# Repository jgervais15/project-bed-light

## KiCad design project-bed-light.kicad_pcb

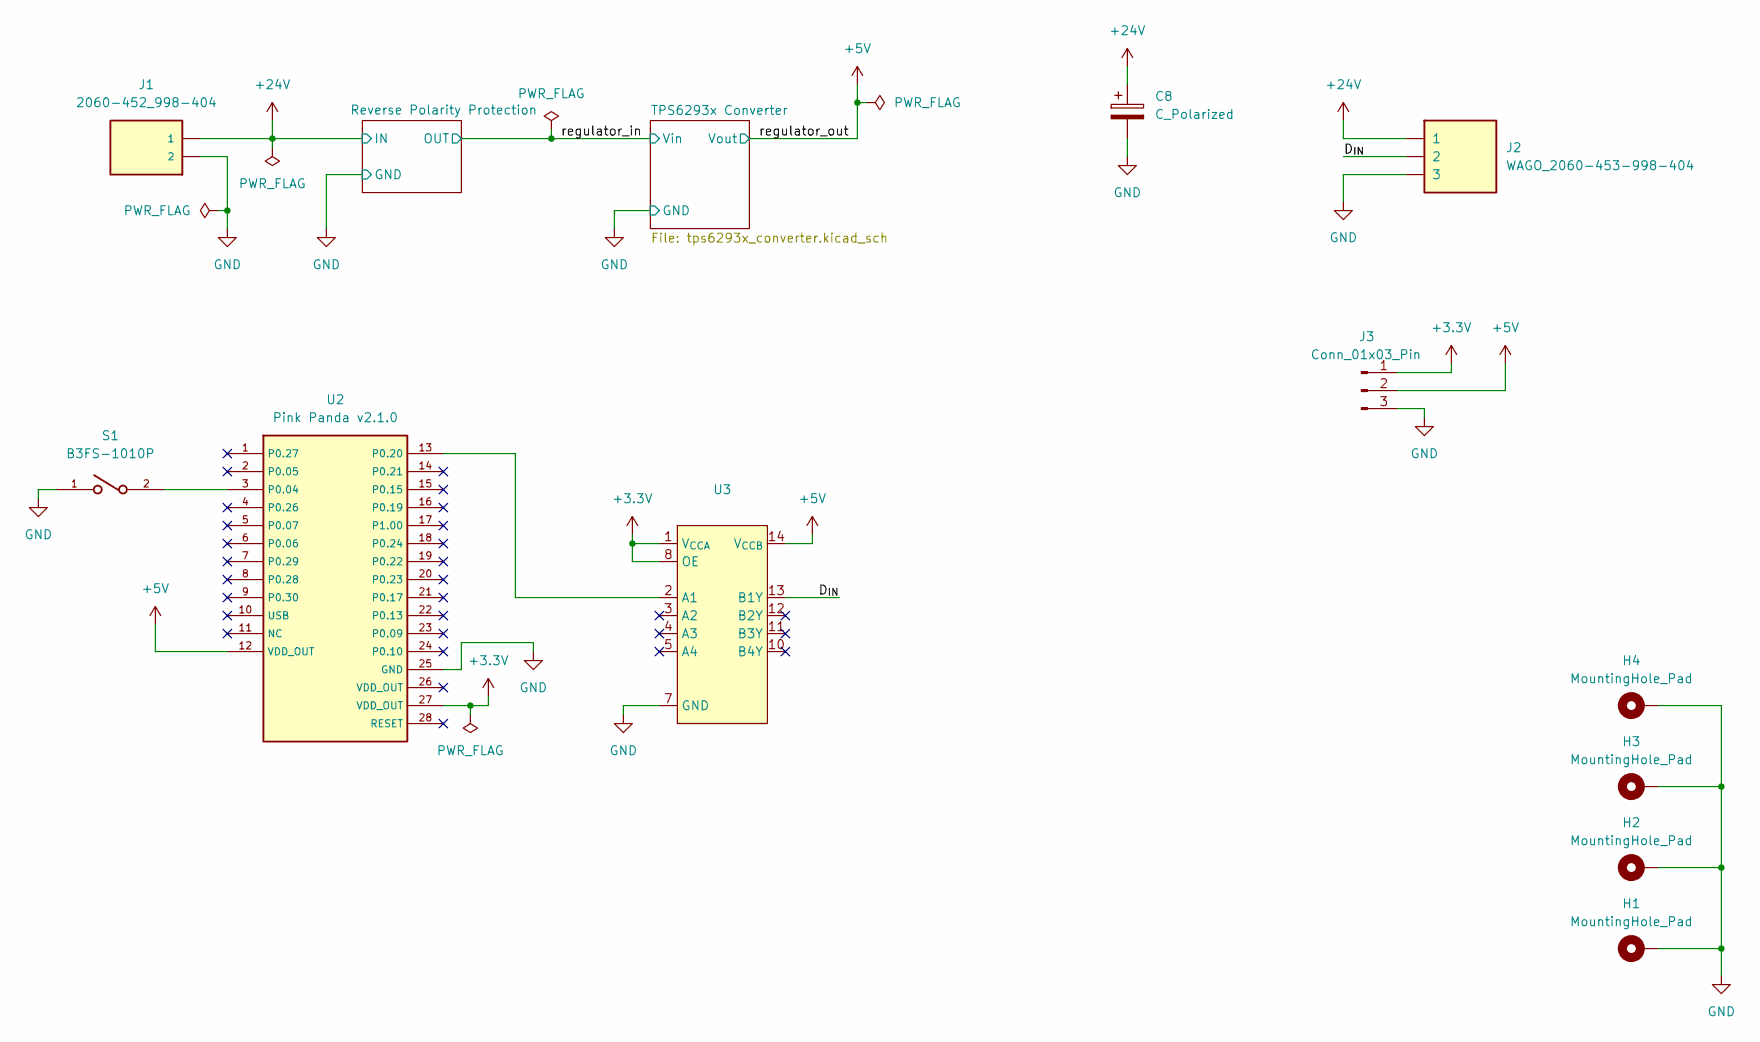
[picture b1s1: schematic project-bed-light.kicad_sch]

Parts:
C8: C_Polarized; CP_Elec_10x10
H1, H2, H3, H4: MountingHole_Pad; MountingHole_2.7mm_M2.5_ISO7380_Pad
J1: 2060-452_998-404; WAGO_2060-452_998-404; PARTREV N/A
J2: WAGO_2060-453-998-404
J3: Conn_01x03_Pin; PinHeader_1x03_P2.54mm_Vertical
S1: B3FS-1010P; SW_B3FS-1010P
U2: Pink Panda v2.1.0; pink_panda_SMD
U3: TSSOP-14_4.4x5mm_P0.65mm

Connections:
+3.3V: J3.1, U2.27 (VDD_OUT), U3.1 (V_{CCA}), U3.8 (OE)
+5V: J3.2, U2.12 (VDD_OUT), U3.14 (V_{CCB}); also elsewhere on the board
+24V: C8.1, J1.1_1 (1), J1.1_2 (1), J2.1_1 (1), J2.1_2 (1); also elsewhere on the board
/D_{IN}: J2.2_1 (2), J2.2_2 (2), U3.13 (B1Y)
GND: C8.2, H1.1, H2.1, H3.1, H4.1, J1.2_1 (2), J1.2_2 (2), J2.3_1 (3), J2.3_2 (3), J3.3, S1.1, U2.25 (GND), U3.7 (GND); also elsewhere on the board
unnamed: S1.2, U2.3 (P0.04)
unnamed: U2.13 (P0.20), U3.2 (A1)

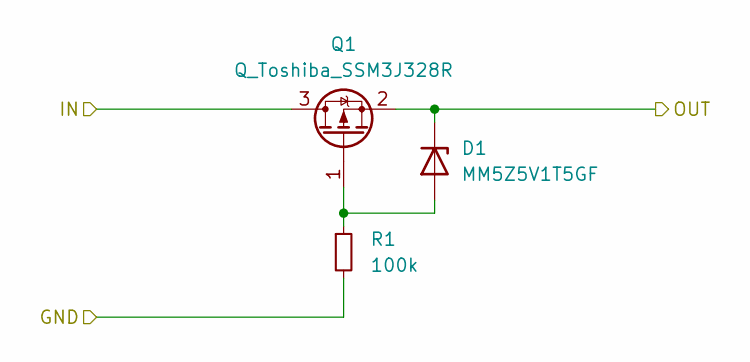
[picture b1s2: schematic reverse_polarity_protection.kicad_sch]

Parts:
D1: MM5Z5V1T5GF; D_SOD-523
Q1: Q_Toshiba_SSM3J328R; SOT-23F
R1: 100k; R_0603_1608Metric

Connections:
+24V: Q1.3 (D); also elsewhere on the board
/regulator_in: D1.1 (K), Q1.2 (S); also elsewhere on the board
GND: R1.2; also elsewhere on the board
unnamed: D1.2 (A), Q1.1 (G), R1.1

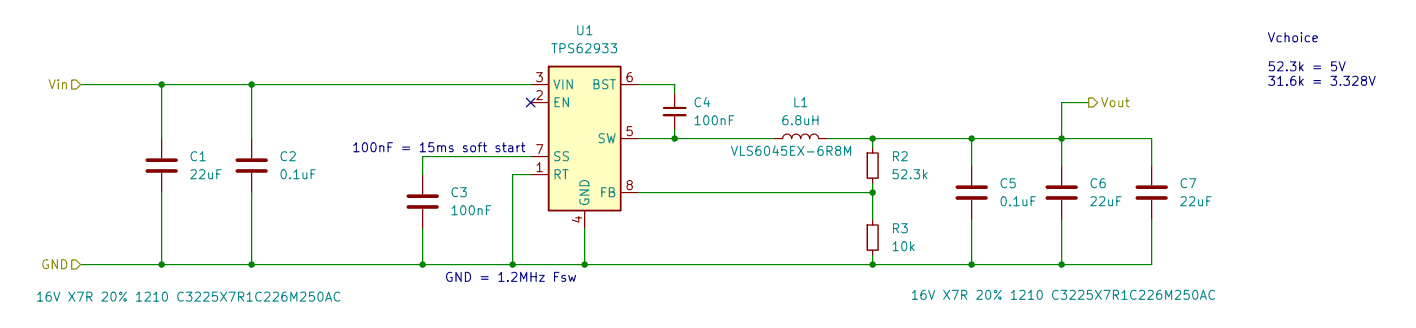
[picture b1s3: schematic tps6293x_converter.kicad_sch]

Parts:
C1, C6, C7: 22uF; C_1210_3225Metric
C2, C5: 0.1uF; C_0603_1608Metric
C3, C4: 100nF; C_0603_1608Metric
L1: 6.8uH; L_TDK_VLS6045EX_VLS6045AF
R2: 52.3k; R_0603_1608Metric
R3: 10k; R_0603_1608Metric
U1: TPS62933; SOT-583-8

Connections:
+5V: C5.1, C6.1, C7.1, L1.2, R2.1; also elsewhere on the board
/regulator_in: C1.1, C2.1, U1.3 (VIN); also elsewhere on the board
GND: C1.2, C2.2, C3.2, C5.2, C6.2, C7.2, R3.2, U1.1 (RT), U1.4 (GND); also elsewhere on the board
unnamed: C4.1, U1.6 (BST)
unnamed: R2.2, R3.1, U1.8 (FB)
unnamed: C3.1, U1.7 (SS)
unnamed: C4.2, L1.1, U1.5 (SW)

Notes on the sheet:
100nF = 15ms soft start
Vchoice 52.3k = 5V 31.6k = 3.328V
GND = 1.2MHz Fsw

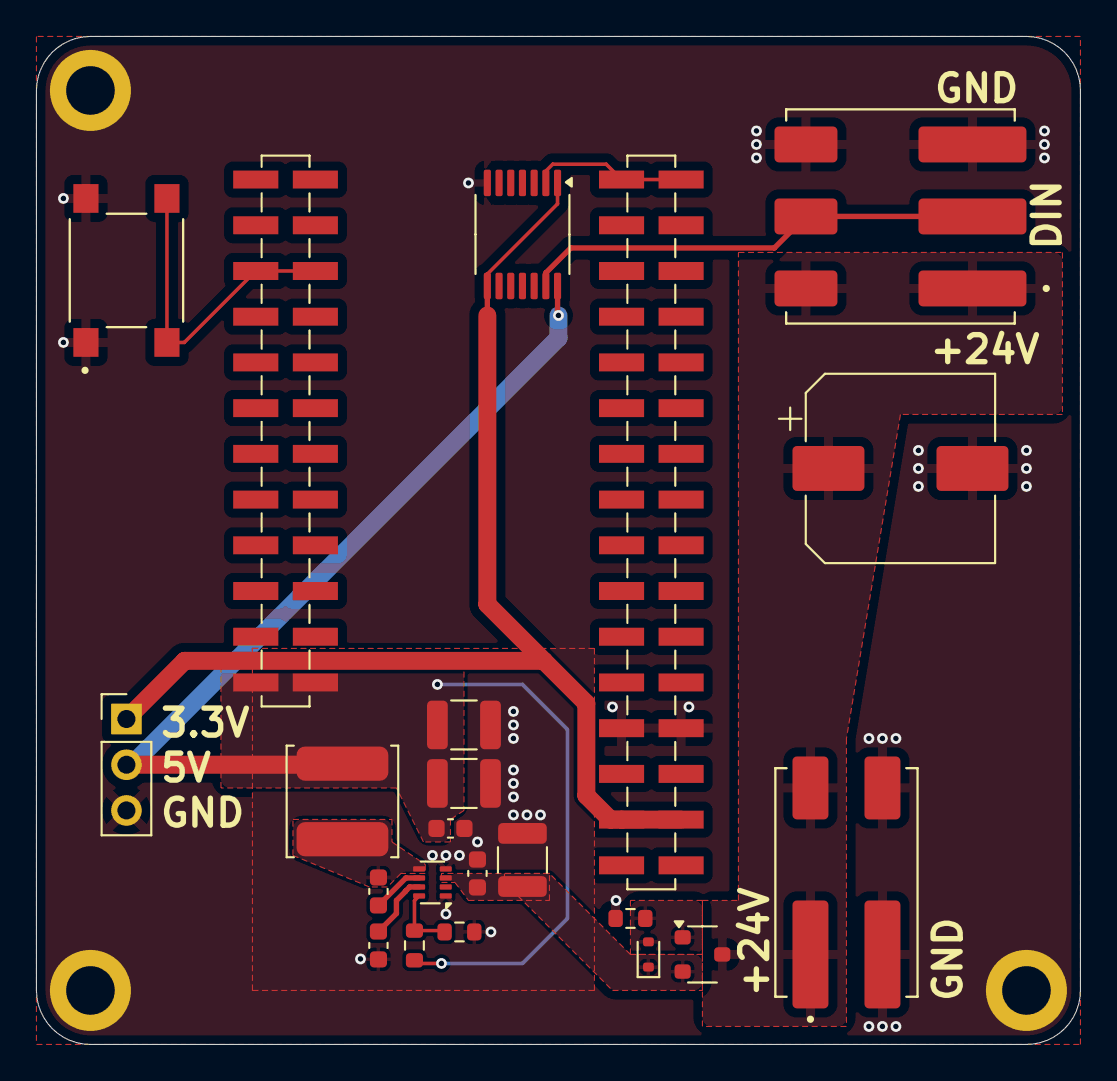
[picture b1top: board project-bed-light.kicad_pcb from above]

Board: 2 copper layers, 58.0 x 56.0 mm, 24 parts (0 on the bottom side), 13 nets.

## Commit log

2025-11-13 New blank project
2025-11-13 Update to kicad 9
2025-11-14 Create schematic
2025-11-17 sch: first draft
2025-11-17 sch: add mounting holes
2025-11-17 sch: add power header
2025-11-23 sch: add 24V cap
2025-11-28 pcb: first placement
2025-11-28 pcb: rotate regulator section
2025-12-22 pcb: route 24V
2025-12-22 pcb: route all power
2025-12-23 pcb: finish routing
2025-12-23 pcb: add all GND vias
2025-12-23 Add gerbers
2025-12-24 pcb: add name
2025-12-24 pcb: couple little changes
2025-12-24 Update gerbers
2026-01-05 pcb: place fab layer
2026-01-05 Add assembly file
